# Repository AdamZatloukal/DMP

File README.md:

# DMP
Dlouhodobá maturitní práce - Člověče nezlob se!

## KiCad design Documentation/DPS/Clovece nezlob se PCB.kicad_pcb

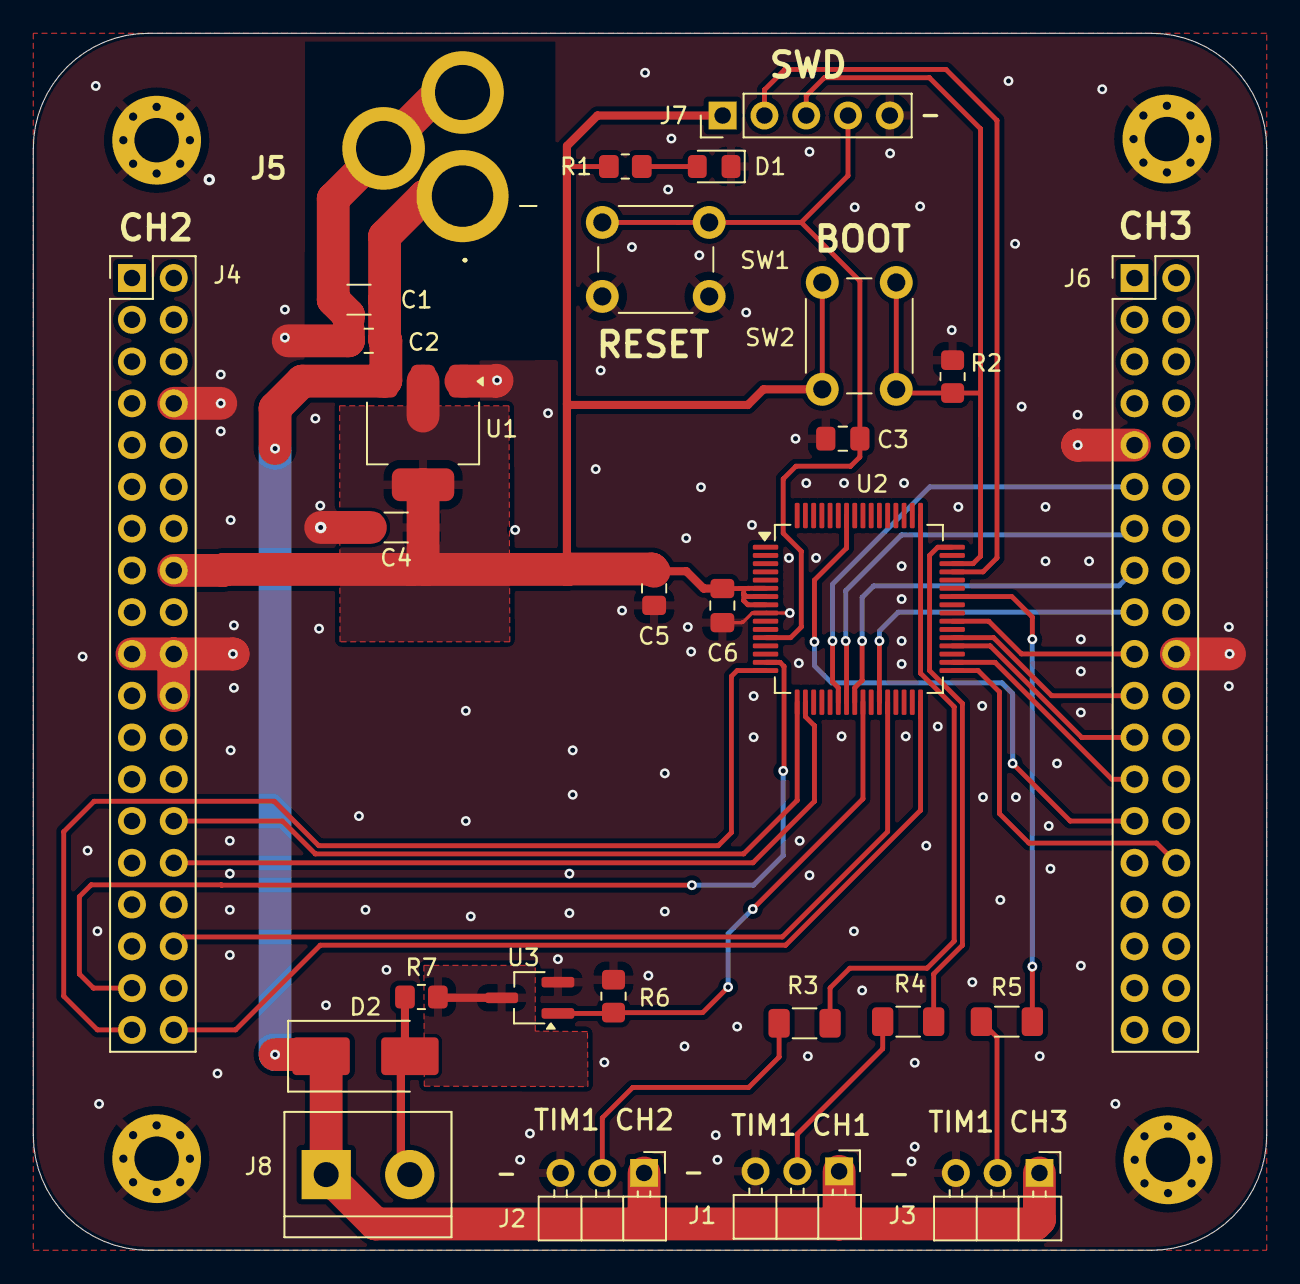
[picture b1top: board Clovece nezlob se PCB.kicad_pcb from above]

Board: 2 copper layers, 75.0 x 74.0 mm, 32 parts (0 on the bottom side), 32 nets.

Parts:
C1, C4: 47u; C_1206_3216Metric_Pad1.33x1.80mm_HandSolder
C2, C3, C6: 100n; C_0805_2012Metric_Pad1.18x1.45mm_HandSolder
C5: 10u; C_0805_2012Metric_Pad1.18x1.45mm_HandSolder
D1: RED; LED_0805_2012Metric_Pad1.15x1.40mm_HandSolder
D2: D; D_SMB_Handsoldering
H1, H2, H3, H4: MountingHole_Pad; MountingHole_2.7mm_M2.5_Pad_Via
J1, J2, J3: Conn_01x03; PinHeader_1x03_P2.54mm_Horizontal
J4, J6: Conn_02x19_Odd_Even; PinHeader_2x19_P2.54mm_Vertical
J5: DCJ200-10-A-K1-K; DCJ20010AK1K
J7: Conn_01x05; PinHeader_1x05_P2.54mm_Vertical
J8: Screw_Terminal_01x02; TerminalBlock_bornier-2_P5.08mm
R1, R7: 1k; R_0805_2012Metric_Pad1.20x1.40mm_HandSolder
R2, R6: 10k; R_0805_2012Metric_Pad1.20x1.40mm_HandSolder
R3, R4, R5: 100R; R_1206_3216Metric_Pad1.30x1.75mm_HandSolder
SW1: SW_Push; SW_PUSH_6mm_H9.5mm
SW2: SW_Push; SW_PUSH_6mm_H4.3mm
U1: LD1117S33TR; SOT-223-3_TabPin2
U2: STM32G071RBT6; LQFP-64_10x10mm_P0.5mm
U3: PJA3404_R1_00001; TSOT-23_HandSoldering

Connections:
+3.3V: C4.1, C5.1, C6.1, J4.16, J7.1, R1.1, SW2.1, U1.2 (VO), U2.6 (VBAT), U2.7 (VREF+), U2.8 (VDD/VDDA)
+5V: C1.1, C2.2, D2.1 (K), J1.1, J2.1, J3.1, J5.1, J8.1, U1.3 (VI)
DISP_NREST (PA1): J4.30, U2.18 (PA1)
DISP_TE (PA0): J4.28, U2.17 (PA0)
GND: C1.2, C2.1, C3.2, C4.2, C5.2, C6.2, D1.1 (K), H1.1, H2.1, H3.1, H4.1, J1.3, J2.3, J3.3, J4.8, J4.19, J4.20, J4.22, J5.2, J5.3, J6.9, J6.20, J7.5, R2.1, R6.2, SW1.2, U1.1 (GND), U2.9 (VSS/VSSA), U3.2
KEY_CENTER (PC7): J6.19, U2.39 (PC7)
KEY_DOWN (PB4): J6.27, U2.58 (PB4)
KEY_LEFT (PB0): J6.17, U2.27 (PB0)
KEY_RIGHT (PB1): J4.34, U2.28 (PB1)
KEY_UP (PB12): J4.38, U2.32 (PB12)
NRST: C3.1, J7.4, SW1.1, U2.12 (PF2-NRST)
unnamed: D1.2 (A), R1.2
unnamed: D2.2 (A), J8.2, R7.2
unnamed: R7.1, U3.3
unnamed: R5.1, U2.42 (PA10)
unnamed: R4.1, U2.48 (PC8)
unnamed: R3.1, U2.49 (PC9)
SPEAKER: R6.1, U2.25 (PC4), U3.1
SPIA_DCX (PB14): J6.25, U2.34 (PB14)
SPIA_MISO (PA6): J6.13, U2.23 (PA6)
SPIA_MOSI (PA7): J6.15, U2.24 (PA7)
SPIA_NCS (PA9): J6.21, U2.37 (PA9)
SPIA_SCK (PA5): J6.11, U2.22 (PA5)
SPIB_MISO (PC2): J4.35, U2.15 (PC2)
SPIB_MOSI (PC3): J4.37, U2.16 (PC3)
SPIB_NCS (PA8): J6.23, U2.36 (PA8)
SPIB_SCK (PB13): J6.30, U2.33 (PB13)
SW_CLK: J7.3, R2.2, SW2.2, U2.46 (PA14-BOOT0)
SW_DIO: J7.2, U2.45 (PA13)
TIM1_CH1: J1.2, R4.2
TIM1_CH2: J2.2, R3.2
TIM1_CH3: J3.2, R5.2

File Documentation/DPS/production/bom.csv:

Designator,Footprint,Quantity,Value,LCSC Part #
"C1, C4",1206,2,47u,
"C2, C3, C6",0805,3,100n,
C5,0805,1,10u,
D1,0805,1,RED,
D2,D_SMB_Handsoldering,1,D,
"J1, J2, J3",PinHeader_1x03_P2.54mm_Horizontal,3,Conn_01x03,
"J4, J6",PinHeader_2x19_P2.54mm_Vertical,2,Conn_02x19_Odd_Even,
J5,DCJ20010AK1K,1,DCJ200-10-A-K1-K,
J7,PinHeader_1x05_P2.54mm_Vertical,1,Conn_01x05,
J8,TerminalBlock_bornier-2_P5.08mm,1,Screw_Terminal_01x02,
"R1, R7",0805,2,1k,
"R2, R6",0805,2,10k,
"R3, R4, R5",1206,3,100R,
SW1,SW_PUSH_6mm_H9.5mm,1,SW_Push,
SW2,SW_PUSH_6mm_H4.3mm,1,SW_Push,
U1,SOT-223-3_TabPin2,1,LD1117S33TR,
U2,LQFP-64_10x10mm_P0.5mm,1,STM32G071RBT6,
U3,TSOT-23_HandSoldering,1,PJA3404_R1_00001,

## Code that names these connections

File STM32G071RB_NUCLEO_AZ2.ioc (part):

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Mcu.Name=STM32G071R(6-8-B)Tx
Mcu.Package=LQFP64
Mcu.UserName=STM32G071RBTx
PA0.GPIOParameters=GPIO_Label,GPIO_ModeDefaultEXTI
PA0.GPIO_Label=DISPLAY_TEARING_EFFECT
PA0.GPIO_ModeDefaultEXTI=GPIO_MODE_IT_RISING_FALLING
PA0.Signal=GPXTI0
PA1.GPIOParameters=GPIO_Speed,GPIO_PuPd,GPIO_Label
PA1.GPIO_Label=DISPLAY_RESET
PA1.GPIO_PuPd=GPIO_NOPULL
PA1.GPIO_Speed=GPIO_SPEED_FREQ_HIGH
PA1.Signal=GPIO_Output
PA10.Signal=S_TIM1_CH3
PA13.Mode=Serial_Wire
PA13.Signal=SYS_SWDIO
PA14-BOOT0.Mode=Serial_Wire
PA14-BOOT0.Signal=SYS_SWCLK
PA5.GPIOParameters=GPIO_Speed,GPIO_PuPd
PA5.GPIO_PuPd=GPIO_PULLDOWN
PA5.GPIO_Speed=GPIO_SPEED_FREQ_HIGH
PA5.Mode=Full_Duplex_Master
PA5.Signal=SPI1_SCK
PA6.GPIOParameters=GPIO_PuPd
PA6.GPIO_PuPd=GPIO_PULLDOWN
PA6.Mode=Full_Duplex_Master
PA6.Signal=SPI1_MISO
PA7.GPIOParameters=GPIO_Speed,GPIO_PuPd
PA7.GPIO_PuPd=GPIO_PULLDOWN
PA7.GPIO_Speed=GPIO_SPEED_FREQ_HIGH
PA7.Mode=Full_Duplex_Master
PA7.Signal=SPI1_MOSI
PA8.GPIOParameters=GPIO_Speed,PinState,GPIO_Label
PA8.GPIO_Label=FLASH_CS
PA8.GPIO_Speed=GPIO_SPEED_FREQ_VERY_HIGH
PA8.PinState=GPIO_PIN_SET
PA8.Signal=GPIO_Output
PA9.GPIOParameters=GPIO_Speed,PinState,GPIO_Label
PA9.GPIO_Label=DISPLAY_CSX
PA9.GPIO_Speed=GPIO_SPEED_FREQ_VERY_HIGH
PA9.PinState=GPIO_PIN_SET
PA9.Signal=GPIO_Output
PB0.GPIOParameters=GPIO_PuPd,GPIO_Label
PB0.GPIO_Label=BUTTON_LEFT
PB0.GPIO_PuPd=GPIO_PULLUP
PB0.Signal=GPIO_Input
PB1.GPIOParameters=GPIO_PuPd,GPIO_Label
PB1.GPIO_Label=BUTTON_RIGHT
PB1.GPIO_PuPd=GPIO_PULLUP
PB1.Signal=GPIO_Input
PB12.GPIOParameters=GPIO_PuPd,GPIO_Label
PB12.GPIO_Label=BUTTON_UP
PB12.GPIO_PuPd=GPIO_PULLUP
PB12.Signal=GPIO_Input
PB13.GPIOParameters=GPIO_Speed,GPIO_PuPd
PB13.GPIO_PuPd=GPIO_PULLDOWN
PB13.GPIO_Speed=GPIO_SPEED_FREQ_HIGH
PB13.Mode=Full_Duplex_Master
PB13.Signal=SPI2_SCK
PB14.GPIOParameters=GPIO_Speed,PinState,GPIO_Label
PB14.GPIO_Label=DISPLAY_DCX
PB14.GPIO_Speed=GPIO_SPEED_FREQ_VERY_HIGH
PB14.PinState=GPIO_PIN_SET
PB14.Signal=GPIO_Output
PB4.GPIOParameters=GPIO_PuPd,GPIO_Label
PB4.GPIO_Label=BUTTON_DOWN
PB4.GPIO_PuPd=GPIO_PULLUP
PB4.Signal=GPIO_Input
PC13.GPIOParameters=GPIO_PuPd,GPIO_Label
PC13.GPIO_Label=BUTTON_USER
PC13.GPIO_PuPd=GPIO_PULLUP
PC13.Signal=GPIO_Input
PC2.GPIOParameters=GPIO_Speed,GPIO_PuPd
PC2.GPIO_PuPd=GPIO_PULLDOWN
PC2.GPIO_Speed=GPIO_SPEED_FREQ_HIGH
PC2.Mode=Full_Duplex_Master
PC2.Signal=SPI2_MISO
PC3.GPIOParameters=GPIO_Speed,GPIO_PuPd
PC3.GPIO_PuPd=GPIO_PULLDOWN
PC3.GPIO_Speed=GPIO_SPEED_FREQ_HIGH
PC3.Mode=Full_Duplex_Master
PC3.Signal=SPI2_MOSI
PC7.GPIOParameters=GPIO_PuPd,GPIO_Label
PC7.GPIO_Label=BUTTON_CENTER
PC7.GPIO_PuPd=GPIO_PULLUP
PC7.Signal=GPIO_Input
PC8.Signal=S_TIM1_CH1
PC9.Signal=S_TIM1_CH2
PF2\ -\ NRST.Signal=GPIO_Output
RCC.HSE_VALUE=8000000
RCC.SYSCLKFreq_VALUE=64000000
RCC.SYSCLKSource=RCC_SYSCLKSOURCE_PLLCLK
board=NUCLEO-G071RB

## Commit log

2024-10-29 Inicializace projektu v STM32CubeIDE
2024-10-30 Inicilaizace TIM1 pro generování PWM
2024-10-30 Driver pro ws2812b
2024-11-01 Komentáře
2024-11-04 Přidání funkce pro změny kanálu PWM na TIM1
    Každý kanál bude ovládat blok hrací desky (jednodušší indexování)
2024-11-05 Opraveno ukončení PWM
    PWM se vypne na základě zvoleného kanálu TIM1
2024-11-09 Prototyp ovládání více kanálů PWM
    Není zcela funkční - asi zvlášť udělat pwm_data pro každý kanál zvlášť
2024-11-10 Více kanálové PWM
    Není dokončeno
2024-11-12 Finalizace vícekanálového PWM
    To do: využití structů a enumů pro přehlednost
2024-11-14 Nastavení jasu
    Vyzkoušet jesli jde nastavit jas na jednotlivých LED (asi ne)
2024-11-16 Lepší struktura a individuální nastavování jasu
2024-11-18 Začátek logiky hry
    základ pro nasazení figurky, výběr structu na základě hrajícího hráče
2024-11-19 Nasazení figurky na hrací desku
2024-11-20 Posun figurky po hrací desce
2024-11-20 Dokumentace, Přesunutí za začátek BOARD části
2024-11-21 Vyhození figurky z hracího pole
2024-11-21 Začátek logiky konečného domečku
2024-11-22 Koncový domeček, oprava chyb
    Zvyšování figurek v domečku na 12 (chyba v podmínce při vyhazování
    hráče)
    Hráč 4 na startu se nastaví na žlutou (protože žlutých figurek na startu
    bylo až 12)
    Zelená figurka zůstane na startu i po dání na hrací desku (asi opraveno
    při předchozích chybách)
2024-11-22 Všechny figurky do cíle - funguje
2024-11-23 Překrytí figurek
    NEFUNGUJE a není dodělané
2024-11-25 Animace
2024-11-25 Oprava chyb u animací
    Správná aktualizace pozice při animaci vyhození figurky
2024-11-26 Animace cíle, dokumentace
2024-11-28 Test
2024-12-05 Výběr figurky na displeji
2025-03-29 readme
2025-04-01 Opravená dokumentace, DPS, model
2025-04-02 Dokumentace
2025-04-09 Licence
2025-05-26 Vyhození hráče
2025-05-28 branch
2025-06-06 Opravena viditelnost 6 po hodu kostkou
2025-06-06 Oprava viditelnosti 6 po hodu kostkou
2025-06-06 Test1
2025-06-06 Test2
2025-06-06 Oprava viditelnosti kostky 2
2025-06-06 úprava UI - startGame
2025-06-06 Opraven problém s circle objektem
2025-06-06 UI update (přidat více obrázků k Screen1 animaci)
2025-06-07 Loading screen
2025-06-07 UI - finalizace1
2025-06-07 GUI - finalizace2
2025-06-07 opravena chyba https://github.com/AdamZatloukal/DMP/issues/5
2025-06-07 Opravena chyba https://github.com/AdamZatloukal/DMP/issues/6
2025-06-09 přeskočení animace na Screen1
2025-06-09 Přidáno https://github.com/AdamZatloukal/DMP/issues/3
2025-06-09 Opraveno https://github.com/AdamZatloukal/DMP/issues/9, vylepšeno https://github.com/AdamZatloukal/DMP/issues/3
2025-06-09 Přidáno https://github.com/AdamZatloukal/DMP/issues/10
2025-06-10 Opraveno https://github.com/AdamZatloukal/DMP/issues/13
2025-06-10 Přidáno https://github.com/AdamZatloukal/DMP/issues/14
2025-06-10 Opraveno https://github.com/AdamZatloukal/DMP/issues/12
2025-06-10 Opraveno https://github.com/AdamZatloukal/DMP/issues/11
2025-06-10 Opraveno https://github.com/AdamZatloukal/DMP/issues/15
2025-06-11 Přidáno https://github.com/AdamZatloukal/DMP/issues/18
2025-06-13 Opraveno: https://github.com/AdamZatloukal/DMP/issues/19
2025-06-13 Opraveno https://github.com/AdamZatloukal/DMP/issues/22 (asi - těžko se replikuje)
2025-06-13 Opraveno https://github.com/AdamZatloukal/DMP/issues/20
2025-06-13 Opraveno https://github.com/AdamZatloukal/DMP/issues/24
2025-06-13 Opraveno https://github.com/AdamZatloukal/DMP/issues/2
2025-06-14 Změněna délka animace v nastavení na 500ms
2025-06-14 Opraveno https://github.com/AdamZatloukal/DMP/issues/23
2025-06-14 Přidáno https://github.com/AdamZatloukal/DMP/issues/21
2025-08-24 obrázky
2025-08-24 overview video
2025-08-24 overview gif
2025-08-30 loading gif
2025-08-30 Removed spinner gif :(
